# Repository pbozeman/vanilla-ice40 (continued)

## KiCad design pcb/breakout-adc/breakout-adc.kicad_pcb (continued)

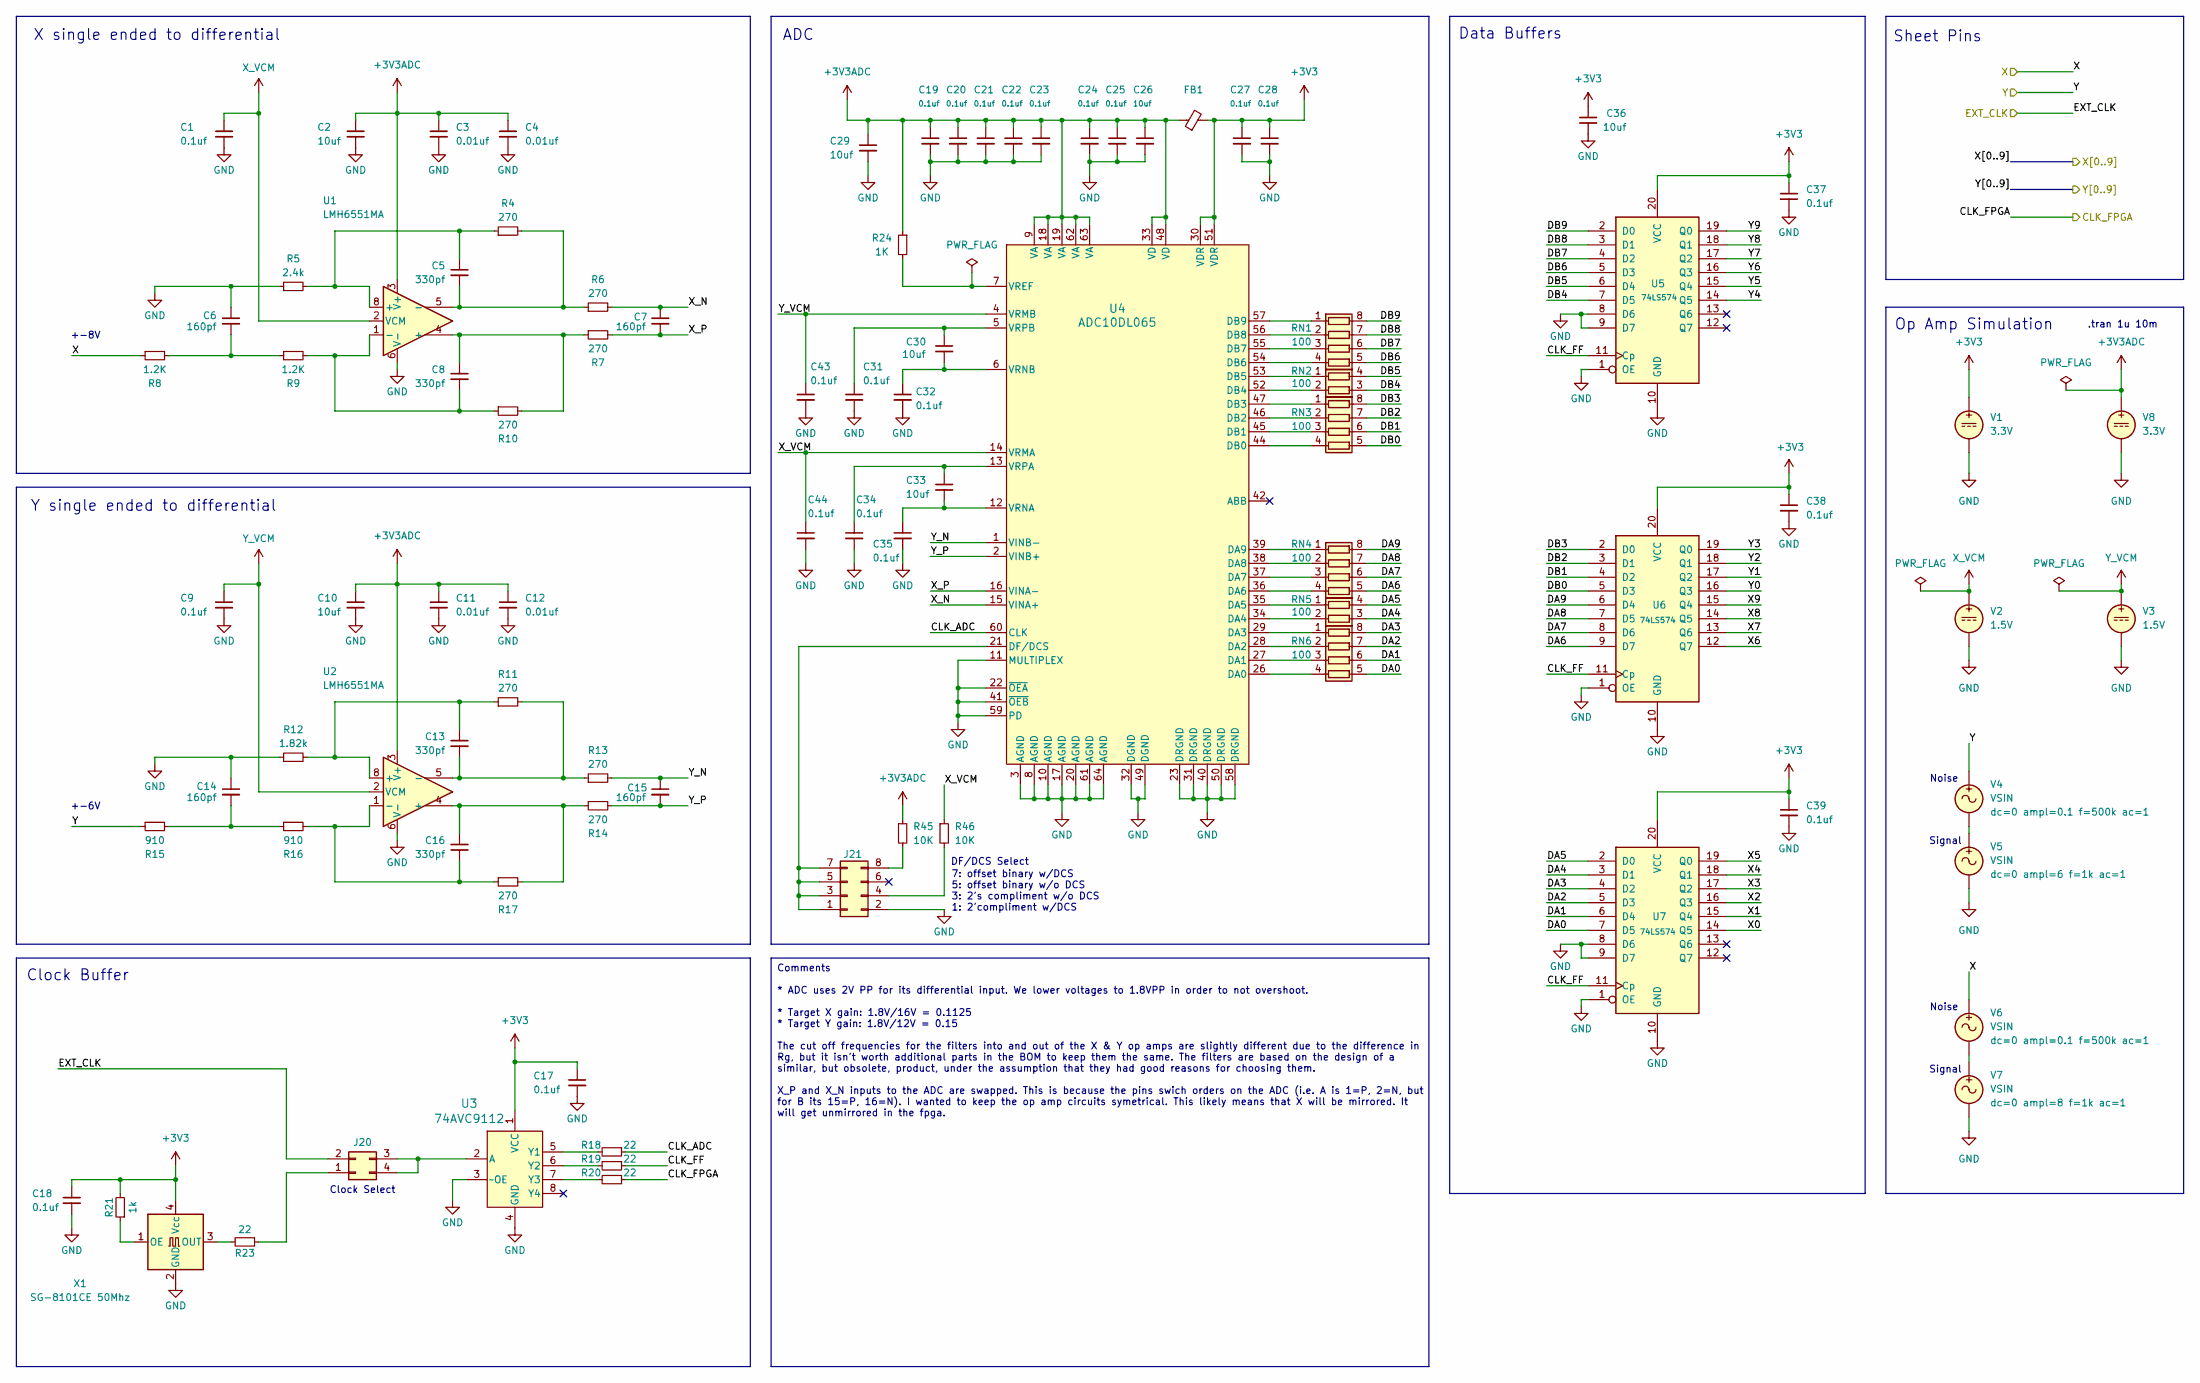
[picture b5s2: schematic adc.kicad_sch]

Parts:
C1, C9, C17, C18, C19, C20, C21, C22, C23, C24, C25, C27, C28, C31, C32, C34, C35, C37, C38, C39, C43, C44: 0.1uf; C_0402_1005Metric; LCSC Part # C71629
C2, C10, C26, C29, C30, C33, C36: 10uf; C_0603_1608Metric; LCSC Part # C77041
C3, C4, C11, C12: 0.01uf; C_0402_1005Metric; LCSC Part # C85735
C5, C8, C13, C16: 330pf; C_0402_1005Metric; Digi-Key Part Number 490-3247-1-ND
C6, C7, C14, C15: 160pf; C_0402_1005Metric; Digi-Key Part Number 490-GRT1555C1H161FA02DCT-ND
FB1: L_0603_1608Metric; LCSC Part # C1002
J20: Conn_02x02_Counter_Clockwise; PinHeader_2x02_P2.54mm_Vertical; Digi-Key Part Number 952-2119-ND
J21: Conn_02x04_Odd_Even; PinHeader_2x04_P2.54mm_Vertical; Digi-Key Part Number 952-2122-ND
R4, R6, R7, R10, R11, R13, R14, R17: 270; R_0603_1608Metric; Digi-Key Part Number YAG1606CT-ND
R5: 2.4k; R_0603_1608Metric; Digi-Key Part Number YAG1619CT-ND
R8, R9: 1.2K; R_0603_1608Metric; Digi-Key Part Number YAG1563CT-ND
R12: 1.82k; R_0603_1608Metric; Digi-Key Part Number YAG1575CT-ND
R15, R16: 910; R_0603_1608Metric; Digi-Key Part Number YAG1748CT-ND
R18, R19, R20, R23: 22; R_0603_1608Metric; LCSC Part # C107701
R21: 1k; R_0603_1608Metric; LCSC Part # C22548
R24: 1K; R_0603_1608Metric; Digi-Key Part Number 311-1.00KHRCT-ND
R45, R46: 10K; R_0603_1608Metric; Digi-Key Part Number 311-10.0KHRCT-ND
RN1, RN3, RN4, RN6: 100; R_Array_Concave_4x0402; LCSC Part # C326873
RN2, RN5: 100; R_Array_Convex_2x0402; Digi-Key Part Number 13-YC122-FR-07100RLCT-ND
U1, U2: LMH6551MA; SOIC-8_3.9x4.9mm_P1.27mm; Digi-Key Part Number LMH6551MA/NOPB-ND
U3: 74AVC9112; VSSOP8_SOT765-1_NEX; Digi-Key Part Number 1727-7845-1-ND
U4: ADC10DL065; VEC64A_TEX; Digi-Key Part Number ADC10DL065CIVS/NOPB-ND
U5, U6, U7: 74LS574; TSSOP-20_4.4x6.5mm_P0.65mm; Digi-Key Part Number 296-8532-1-ND
V1, V8: 3.3V
V2, V3: 1.5V
V4, V5, V6, V7: VSIN
X1: SG-8101CE 50Mhz; Oscillator_SMD_SeikoEpson_SG8002CE-4Pin_3.2x2.5mm; LCSC Part # C390556

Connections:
+3V3: C17.1, C18.1, C27.1, C28.1, C36.1, C37.1, C38.1, C39.1, FB1.2, R21.2, U3.1 (VCC), U4.30 (VDR), U4.51 (VDR), U5.20 (VCC), U6.20 (VCC), U7.20 (VCC), V1.1, X1.4 (Vcc); also elsewhere on the board
+3V3ADC: C2.1, C3.1, C4.1, C10.1, C11.1, C12.1, C19.1, C20.1, C21.1, C22.1, C23.1, C24.1, C25.1, C26.1, C29.1, FB1.1, R24.1, R45.1, U1.3 (V+), U2.3 (V+), U4.9 (VA), U4.18 (VA), U4.19 (VA), U4.33 (VD), U4.48 (VD), U4.62 (VA), U4.63 (VA), V8.1; also elsewhere on the board
/X: R8.1, V6.1; also elsewhere on the board
/Y: R15.1, V4.1; also elsewhere on the board
/adc/CLK_ADC: R18.1, U4.60 (CLK)
/adc/CLK_FF: R19.1, U5.11 (Cp), U6.11 (Cp), U7.11 (Cp)
/adc/DA0: RN6.5 (R4.2), U7.7 (D5)
/adc/DA1: RN6.6 (R3.2), U7.6 (D4)
/adc/DA2: RN6.7 (R2.2), U7.5 (D3)
/adc/DA3: RN6.8 (R1.2), U7.4 (D2)
/adc/DA4: RN5.3 (R2.2), U7.3 (D1)
/adc/DA5: RN5.4 (R1.2), U7.2 (D0)
/adc/DA6: RN4.5 (R4.2), U6.9 (D7)
/adc/DA7: RN4.6 (R3.2), U6.8 (D6)
/adc/DA8: RN4.7 (R2.2), U6.7 (D5)
/adc/DA9: RN4.8 (R1.2), U6.6 (D4)
/adc/DB0: RN3.5 (R4.2), U6.5 (D3)
/adc/DB1: RN3.6 (R3.2), U6.4 (D2)
/adc/DB2: RN3.7 (R2.2), U6.3 (D1)
/adc/DB3: RN3.8 (R1.2), U6.2 (D0)
/adc/DB4: RN2.3 (R2.2), U5.7 (D5)
/adc/DB5: RN2.4 (R1.2), U5.6 (D4)
/adc/DB6: RN1.5 (R4.2), U5.5 (D3)
/adc/DB7: RN1.6 (R3.2), U5.4 (D2)
/adc/DB8: RN1.7 (R2.2), U5.3 (D1)
/adc/DB9: RN1.8 (R1.2), U5.2 (D0)
/adc/X_N: C7.1, R6.2, U4.15 (VINA+)
/adc/X_P: C7.2, R7.2, U4.16 (VINA-)
/adc/Y_N: C15.1, R13.2, U4.1 (VINB-)
/adc/Y_P: C15.2, R14.2, U4.2 (VINB+)
D_12: J20.2; also elsewhere on the board
D_16: R20.1; also elsewhere on the board
D_23: U5.19 (Q0); also elsewhere on the board
D_27: U5.18 (Q1); also elsewhere on the board
D_31: U5.17 (Q2); also elsewhere on the board
D_35: U5.16 (Q3); also elsewhere on the board
D_39: U5.15 (Q4); also elsewhere on the board
D_43: U5.14 (Q5); also elsewhere on the board
D_47: U6.19 (Q0); also elsewhere on the board
D_51: U6.18 (Q1); also elsewhere on the board
D_55: U6.17 (Q2); also elsewhere on the board
D_59: U6.16 (Q3); also elsewhere on the board
D_63: U6.15 (Q4); also elsewhere on the board
D_67: U6.14 (Q5); also elsewhere on the board
D_71: U6.13 (Q6); also elsewhere on the board
D_75: U6.12 (Q7); also elsewhere on the board
D_79: U7.19 (Q0); also elsewhere on the board
D_83: U7.18 (Q1); also elsewhere on the board
D_87: U7.17 (Q2); also elsewhere on the board
D_91: U7.16 (Q3); also elsewhere on the board
D_95: U7.15 (Q4); also elsewhere on the board
D_99: U7.14 (Q5); also elsewhere on the board
GND: C1.2, C2.2, C3.2, C4.2, C6.1, C9.2, C10.2, C11.2, C12.2, C14.1, C17.2, C18.2, C19.2, C20.2, C21.2, C22.2, C23.2, C24.2, C25.2, C26.2, C27.2, C28.2, C29.2, C31.2, C32.2, C34.2, C35.2, C36.2, C37.2, C38.2, C39.2, C43.2, C44.2, J21.2, R5.1, R12.1, U1.6 (V-), U2.6 (V-), U3.3 (~OE), U3.4 (GND), U4.3 (AGND), U4.8 (AGND), U4.10 (AGND), U4.11 (MULTIPLEX), U4.17 (AGND), U4.20 (AGND), U4.22 (~OEA), U4.23 (DRGND), U4.31 (DRGND), U4.32 (DGND), U4.40 (DRGND), U4.41 (~OEB), U4.49 (DGND), U4.50 (DRGND), U4.58 (DRGND), U4.59 (PD), U4.61 (AGND), U4.64 (AGND), U5.1 (OE), U5.8 (D6), U5.9 (D7), U5.10 (GND), U6.1 (OE), U6.10 (GND), U7.1 (OE), U7.8 (D6), U7.9 (D7), U7.10 (GND), V1.2, V2.2, V3.2, V5.2, V7.2, V8.2, X1.2 (GND); also elsewhere on the board
unnamed: C5.1, R4.1, R5.2, U1.8 (+)
unnamed: C5.2, R4.2, R6.1, U1.5 (-)
unnamed: C6.2, R8.2, R9.1
unnamed: C8.1, R7.1, R10.2, U1.4 (+)
unnamed: C8.2, R9.2, R10.1, U1.1 (-)
unnamed: C13.1, R11.1, R12.2, U2.8 (+)
unnamed: C13.2, R11.2, R13.1, U2.5 (-)
unnamed: C14.2, R15.2, R16.1
unnamed: C16.1, R14.1, R17.2, U2.4 (+)
unnamed: C16.2, R16.2, R17.1, U2.1 (-)
unnamed: J20.1, R23.1
unnamed: J20.3, J20.4, U3.2 (A)
unnamed: J21.1, J21.3, J21.5, J21.7, U4.21 (DF/DCS)
unnamed: J21.4, R46.2
unnamed: J21.8, R45.2
unnamed: RN1.1 (R1.1), U4.57 (DB9)
unnamed: RN1.2 (R2.1), U4.56 (DB8)
unnamed: RN1.3 (R3.1), U4.55 (DB7)
unnamed: RN1.4 (R4.1), U4.54 (DB6)
unnamed: RN2.1 (R1.1), U4.53 (DB5)
unnamed: RN2.2 (R2.1), U4.52 (DB4)
unnamed: RN3.1 (R1.1), U4.47 (DB3)
unnamed: RN3.2 (R2.1), U4.46 (DB2)
unnamed: RN3.3 (R3.1), U4.45 (DB1)
unnamed: RN3.4 (R4.1), U4.44 (DB0)
unnamed: RN4.1 (R1.1), U4.39 (DA9)
unnamed: RN4.2 (R2.1), U4.38 (DA8)
unnamed: RN4.3 (R3.1), U4.37 (DA7)
unnamed: RN4.4 (R4.1), U4.36 (DA6)
unnamed: RN5.1 (R1.1), U4.35 (DA5)
unnamed: RN5.2 (R2.1), U4.34 (DA4)
unnamed: RN6.1 (R1.1), U4.29 (DA3)
unnamed: RN6.2 (R2.1), U4.28 (DA2)
unnamed: RN6.3 (R3.1), U4.27 (DA1)
unnamed: RN6.4 (R4.1), U4.26 (DA0)
unnamed: R18.2, U3.5 (Y1)
unnamed: R19.2, U3.6 (Y2)
unnamed: R20.2, U3.7 (Y3)
unnamed: R24.2, U4.7 (VREF)
unnamed: C33.2, C35.1, U4.12 (VRNA)
unnamed: C30.2, C32.1, U4.6 (VRNB)
unnamed: C33.1, C34.1, U4.13 (VRPA)
unnamed: C30.1, C31.1, U4.5 (VRPB)
unnamed: V4.2, V5.1
unnamed: V6.2, V7.1
unnamed: R21.1, X1.1 (OE)
unnamed: R23.2, X1.3 (OUT)
X_VCM: C1.1, C44.1, R46.1, U1.2 (VCM), U4.14 (VRMA), V2.1; also elsewhere on the board
Y_VCM: C9.1, C43.1, U2.2 (VCM), U4.4 (VRMB), V3.1; also elsewhere on the board

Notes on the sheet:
Comments * ADC uses 2V PP for its differential input. We lower voltages to 1.8VPP in order to not overshoot. * Target X gain: 1.8V/16V = 0.1125 * Target Y gain: 1.8V/12V = 0.15 The cut off frequencies for the filters into and out of the X & Y op amps are slightly different due to the difference in 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
Y single ended to differential
7: offset binary w/DCS 5: offset binary w/o DCS 3: 2's compliment w/o DCS 1: 2'compliment w/DCS
+-8V
Signal
Data Buffers
Clock Select
.tran 1u 10m
X single ended to differential
Noise
ADC
Sheet Pins
Op Amp Simulation
+-6V
DF/DCS Select
Clock Buffer

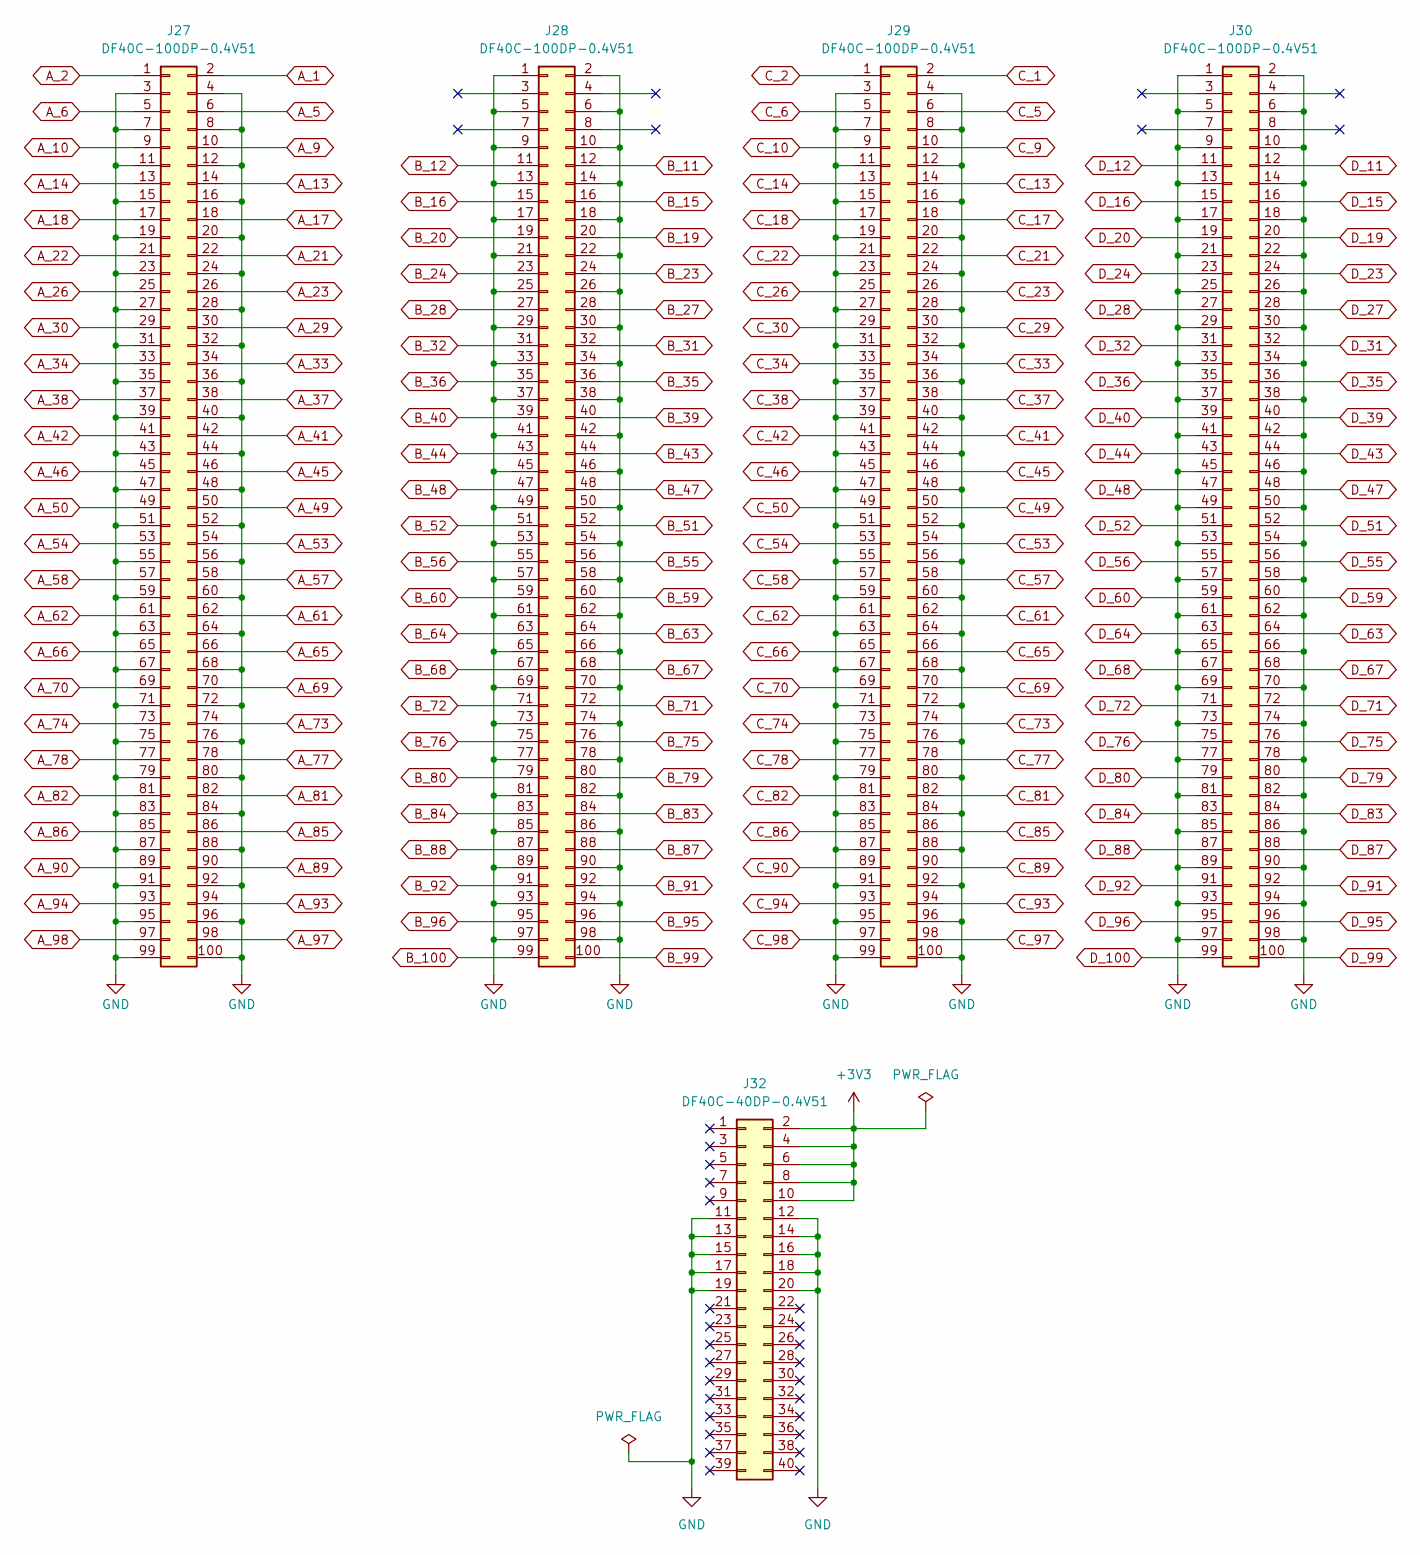
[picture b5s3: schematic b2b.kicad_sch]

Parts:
J27, J28, J29, J30: DF40C-100DP-0.4V51; DF40C100DP04V51; Digi-Key Part Number H11615CT-ND
J32: DF40C-40DP-0.4V51; DF40C40DP04V51; Digi-Key Part Number H11625CT-ND

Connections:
+3V3: J32.2, J32.4, J32.6, J32.8, J32.10; also elsewhere on the board
A_1: J27.2
A_2: J27.1
A_5: J27.6
A_6: J27.5
A_9: J27.10
A_10: J27.9
A_13: J27.14
A_14: J27.13
A_17: J27.18
A_18: J27.17
A_21: J27.22
A_22: J27.21
A_23: J27.26
A_26: J27.25
A_29: J27.30
A_30: J27.29
A_33: J27.34
A_34: J27.33
A_37: J27.38
A_38: J27.37
A_41: J27.42
A_42: J27.41
A_45: J27.46
A_46: J27.45
A_49: J27.50
A_50: J27.49
A_53: J27.54
A_54: J27.53
A_57: J27.58
A_58: J27.57
A_61: J27.62
A_62: J27.61
A_65: J27.66
A_66: J27.65
A_69: J27.70
A_70: J27.69
A_73: J27.74
A_74: J27.73
A_77: J27.78
A_78: J27.77
A_81: J27.82
A_82: J27.81
A_85: J27.86
A_86: J27.85
A_89: J27.90
A_90: J27.89
A_93: J27.94
A_94: J27.93
A_97: J27.98
A_98: J27.97
B_11: J28.12
B_12: J28.11
B_15: J28.16
B_16: J28.15
B_19: J28.20
B_20: J28.19
B_23: J28.24
B_24: J28.23
B_27: J28.28
B_28: J28.27
B_31: J28.32
B_32: J28.31
B_35: J28.36
B_36: J28.35
B_39: J28.40
B_40: J28.39
B_43: J28.44
B_44: J28.43
B_47: J28.48
B_48: J28.47
B_51: J28.52
B_52: J28.51
B_55: J28.56
B_56: J28.55
B_59: J28.60
B_60: J28.59
B_63: J28.64
B_64: J28.63
B_67: J28.68
B_68: J28.67
B_71: J28.72
B_72: J28.71
B_75: J28.76
B_76: J28.75
B_79: J28.80
B_80: J28.79
B_83: J28.84
B_84: J28.83
B_87: J28.88
B_88: J28.87
B_91: J28.92
B_92: J28.91
B_95: J28.96
B_96: J28.95
B_99: J28.100
B_100: J28.99
C_1: J29.2
C_2: J29.1
C_5: J29.6
C_6: J29.5
C_9: J29.10
C_10: J29.9
C_13: J29.14
C_14: J29.13
C_17: J29.18
C_18: J29.17
C_21: J29.22
C_22: J29.21
C_23: J29.26
C_26: J29.25
C_29: J29.30
C_30: J29.29
C_33: J29.34
C_34: J29.33
C_37: J29.38
C_38: J29.37
C_41: J29.42
C_42: J29.41
C_45: J29.46
C_46: J29.45
C_49: J29.50
C_50: J29.49
C_53: J29.54
C_54: J29.53
C_57: J29.58
C_58: J29.57; also elsewhere on the board
C_61: J29.62
C_62: J29.61; also elsewhere on the board
C_65: J29.66
C_66: J29.65; also elsewhere on the board
C_69: J29.70
C_70: J29.69; also elsewhere on the board
C_73: J29.74
C_74: J29.73; also elsewhere on the board
C_77: J29.78
C_78: J29.77; also elsewhere on the board
C_81: J29.82
C_82: J29.81; also elsewhere on the board
C_85: J29.86
C_86: J29.85; also elsewhere on the board
C_89: J29.90
C_90: J29.89; also elsewhere on the board
C_93: J29.94
C_94: J29.93; also elsewhere on the board
C_97: J29.98
C_98: J29.97; also elsewhere on the board
D_11: J30.12; also elsewhere on the board
D_12: J30.11; also elsewhere on the board
D_15: J30.16; also elsewhere on the board
D_16: J30.15; also elsewhere on the board
D_19: J30.20; also elsewhere on the board
D_20: J30.19; also elsewhere on the board
D_23: J30.24; also elsewhere on the board
D_24: J30.23; also elsewhere on the board
D_27: J30.28; also elsewhere on the board
D_28: J30.27; also elsewhere on the board
D_31: J30.32; also elsewhere on the board
D_32: J30.31
D_35: J30.36; also elsewhere on the board
D_36: J30.35
D_39: J30.40; also elsewhere on the board
D_40: J30.39
D_43: J30.44; also elsewhere on the board
D_44: J30.43
D_47: J30.48; also elsewhere on the board
D_48: J30.47
D_51: J30.52; also elsewhere on the board
D_52: J30.51
D_55: J30.56; also elsewhere on the board
D_56: J30.55
D_59: J30.60; also elsewhere on the board
D_60: J30.59
D_63: J30.64; also elsewhere on the board
D_64: J30.63
D_67: J30.68; also elsewhere on the board
D_68: J30.67
D_71: J30.72; also elsewhere on the board
D_72: J30.71
D_75: J30.76; also elsewhere on the board
D_76: J30.75
D_79: J30.80; also elsewhere on the board
D_80: J30.79
D_83: J30.84; also elsewhere on the board
D_84: J30.83
D_87: J30.88; also elsewhere on the board
D_88: J30.87
D_91: J30.92; also elsewhere on the board
D_92: J30.91
D_95: J30.96; also elsewhere on the board
D_96: J30.95
D_99: J30.100; also elsewhere on the board
D_100: J30.99
GND: J27.3, J27.4, J27.7, J27.8, J27.11, J27.12, J27.15, J27.16, J27.19, J27.20, J27.23, J27.24, J27.27, J27.28, J27.31, J27.32, J27.35, J27.36, J27.39, J27.40, J27.43, J27.44, J27.47, J27.48, J27.51, J27.52, J27.55, J27.56, J27.59, J27.60, J27.63, J27.64, J27.67, J27.68, J27.71, J27.72, J27.75, J27.76, J27.79, J27.80, J27.83, J27.84, J27.87, J27.88, J27.91, J27.92, J27.95, J27.96, J27.99, J27.100, J28.1, J28.2, J28.5, J28.6, J28.9, J28.10, J28.13, J28.14, J28.17, J28.18, J28.21, J28.22, J28.25, J28.26, J28.29, J28.30, J28.33, J28.34, J28.37, J28.38, J28.41, J28.42, J28.45, J28.46, J28.49, J28.50, J28.53, J28.54, J28.57, J28.58, J28.61, J28.62, J28.65, J28.66, J28.69, J28.70, J28.73, J28.74, J28.77, J28.78, J28.81, J28.82, J28.85, J28.86, J28.89, J28.90, J28.93, J28.94, J28.97, J28.98, J29.3, J29.4, J29.7, J29.8, J29.11, J29.12, J29.15, J29.16, J29.19, J29.20, J29.23, J29.24, J29.27, J29.28, J29.31, J29.32, J29.35, J29.36, J29.39, J29.40, J29.43, J29.44, J29.47, J29.48, J29.51, J29.52, J29.55, J29.56, J29.59, J29.60, J29.63, J29.64, J29.67, J29.68, J29.71, J29.72, J29.75, J29.76, J29.79, J29.80, J29.83, J29.84, J29.87, J29.88, J29.91, J29.92, J29.95, J29.96, J29.99, J29.100, J30.1, J30.2, J30.5, J30.6, J30.9, J30.10, J30.13, J30.14, J30.17, J30.18, J30.21, J30.22, J30.25, J30.26, J30.29, J30.30, J30.33, J30.34, J30.37, J30.38, J30.41, J30.42, J30.45, J30.46, J30.49, J30.50, J30.53, J30.54, J30.57, J30.58, J30.61, J30.62, J30.65, J30.66, J30.69, J30.70, J30.73, J30.74, J30.77, J30.78, J30.81, J30.82, J30.85, J30.86, J30.89, J30.90, J30.93, J30.94, J30.97, J30.98, J32.11, J32.12, J32.13, J32.14, J32.15, J32.16, J32.17, J32.18, J32.19, J32.20; also elsewhere on the board

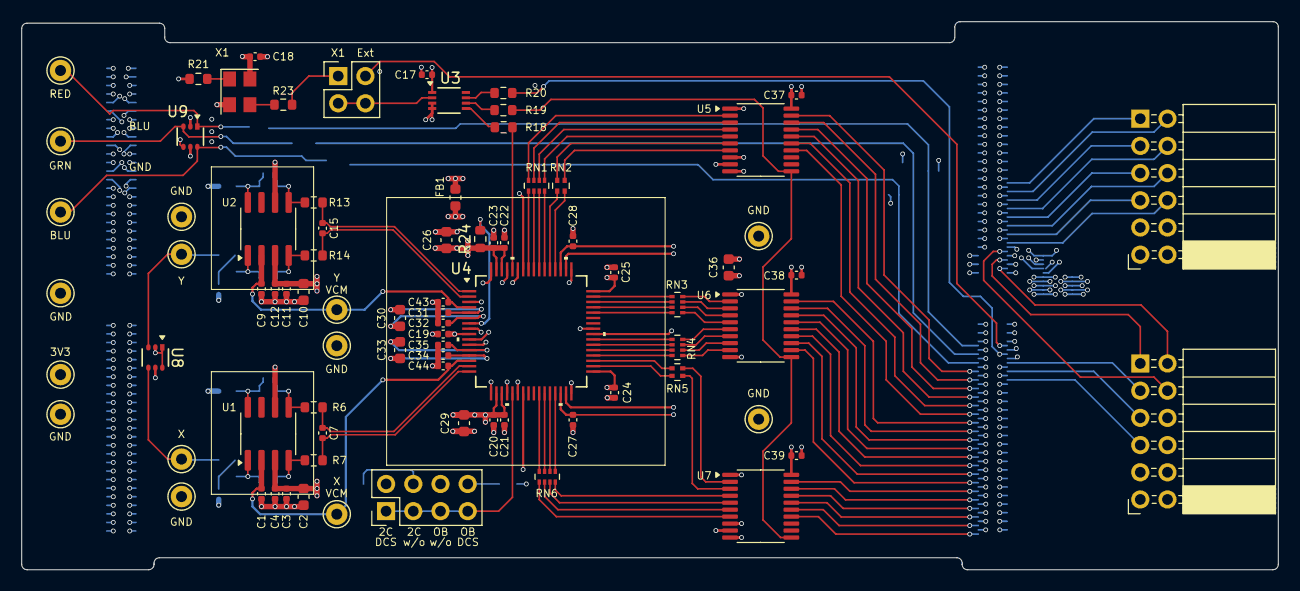
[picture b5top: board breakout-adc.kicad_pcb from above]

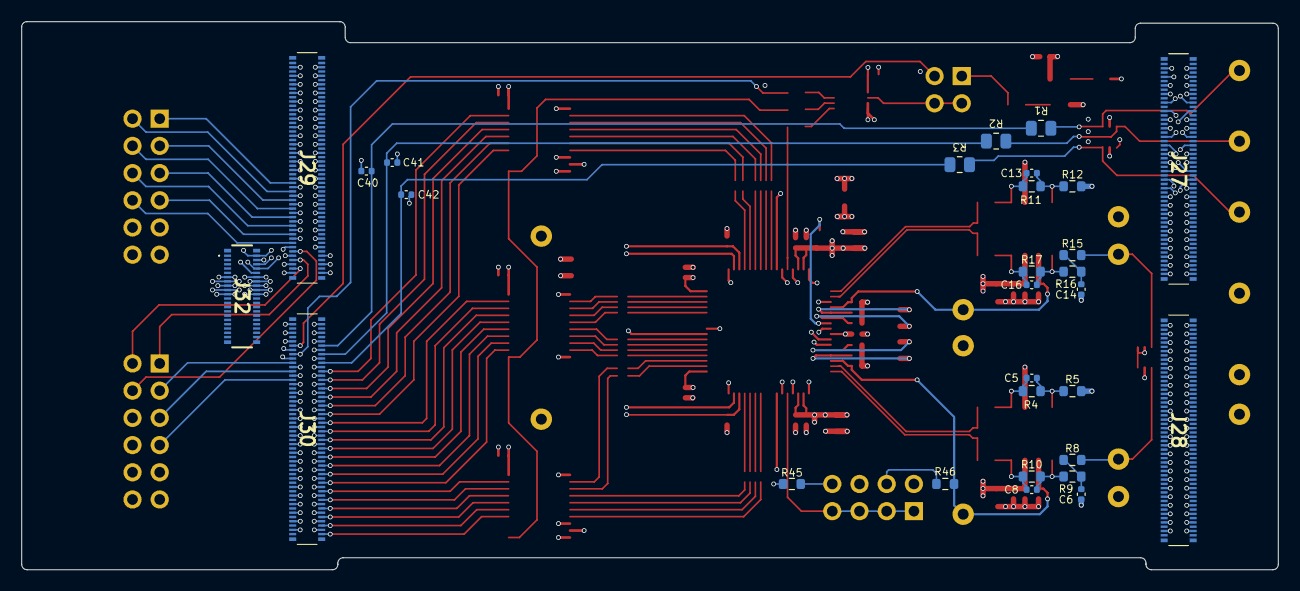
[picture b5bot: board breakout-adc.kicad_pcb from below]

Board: 4 copper layers, 117.4 x 51.2 mm, 110 parts (29 on the bottom side), 120 nets.

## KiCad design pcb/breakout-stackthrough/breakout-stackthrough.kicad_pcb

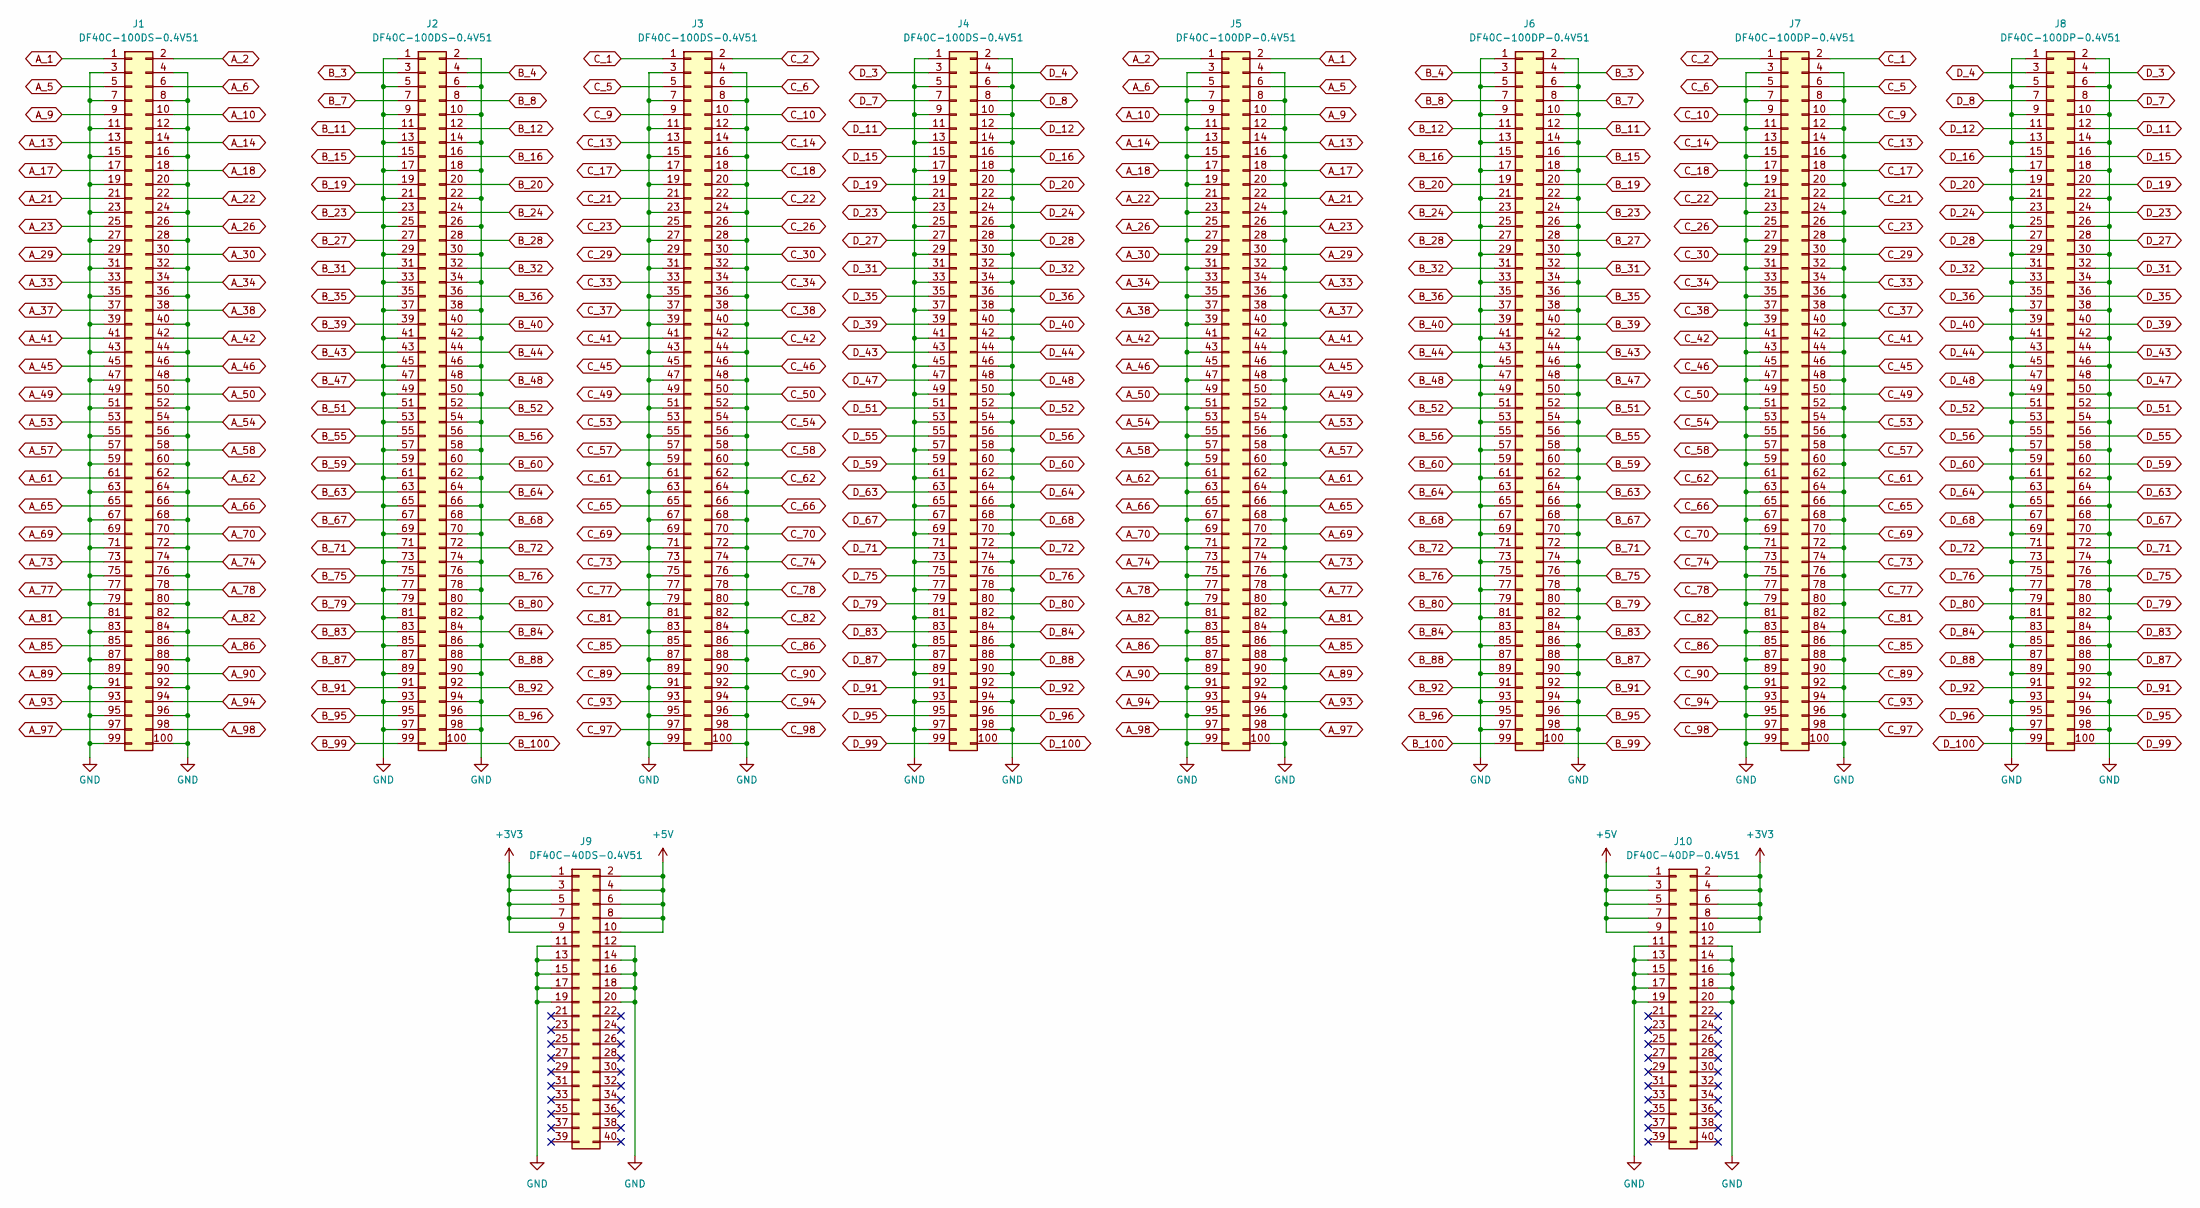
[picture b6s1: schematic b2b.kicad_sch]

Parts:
J1, J2, J3, J4: DF40C-100DS-0.4V51; DF40C100DS04V51; Digi-Key Part Number H11615CT-ND
J5, J6, J7, J8: DF40C-100DP-0.4V51; DF40C100DP04V51; Digi-Key Part Number H11615CT-ND
J9: DF40C-40DS-0.4V51; DF40C40DS04V51; Digi-Key Part Number H11625CT-ND
J10: DF40C-40DP-0.4V51; DF40C40DP04V51; Digi-Key Part Number H11625CT-ND

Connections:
+3V3: J9.1, J9.3, J9.5, J9.7, J9.9, J10.2, J10.4, J10.6, J10.8, J10.10
+5V: J9.2, J9.4, J9.6, J9.8, J9.10, J10.1, J10.3, J10.5, J10.7, J10.9
A_1: J1.1, J5.2
A_2: J1.2, J5.1
A_5: J1.5, J5.6
A_6: J1.6, J5.5
A_9: J1.9, J5.10
A_10: J1.10, J5.9
A_13: J1.13, J5.14
A_14: J1.14, J5.13
A_17: J1.17, J5.18
A_18: J1.18, J5.17
A_21: J1.21, J5.22
A_22: J1.22, J5.21
A_23: J1.25, J5.26
A_26: J1.26, J5.25
A_29: J1.29, J5.30
A_30: J1.30, J5.29
A_33: J1.33, J5.34
A_34: J1.34, J5.33
A_37: J1.37, J5.38
A_38: J1.38, J5.37
A_41: J1.41, J5.42
A_42: J1.42, J5.41
A_45: J1.45, J5.46
A_46: J1.46, J5.45
A_49: J1.49, J5.50
A_50: J1.50, J5.49
A_53: J1.53, J5.54
A_54: J1.54, J5.53
A_57: J1.57, J5.58
A_58: J1.58, J5.57
A_61: J1.61, J5.62
A_62: J1.62, J5.61
A_65: J1.65, J5.66
A_66: J1.66, J5.65
A_69: J1.69, J5.70
A_70: J1.70, J5.69
A_73: J1.73, J5.74
A_74: J1.74, J5.73
A_77: J1.77, J5.78
A_78: J1.78, J5.77
A_81: J1.81, J5.82
A_82: J1.82, J5.81
A_85: J1.85, J5.86
A_86: J1.86, J5.85
A_89: J1.89, J5.90
A_90: J1.90, J5.89
A_93: J1.93, J5.94
A_94: J1.94, J5.93
A_97: J1.97, J5.98
A_98: J1.98, J5.97
B_3: J2.3, J6.4
B_4: J2.4, J6.3
B_7: J2.7, J6.8
B_8: J2.8, J6.7
B_11: J2.11, J6.12
B_12: J2.12, J6.11
B_15: J2.15, J6.16
B_16: J2.16, J6.15
B_19: J2.19, J6.20
B_20: J2.20, J6.19
B_23: J2.23, J6.24
B_24: J2.24, J6.23
B_27: J2.27, J6.28
B_28: J2.28, J6.27
B_31: J2.31, J6.32
B_32: J2.32, J6.31
B_35: J2.35, J6.36
B_36: J2.36, J6.35
B_39: J2.39, J6.40
B_40: J2.40, J6.39
B_43: J2.43, J6.44
B_44: J2.44, J6.43
B_47: J2.47, J6.48
B_48: J2.48, J6.47
B_51: J2.51, J6.52
B_52: J2.52, J6.51
B_55: J2.55, J6.56
B_56: J2.56, J6.55
B_59: J2.59, J6.60
B_60: J2.60, J6.59
B_63: J2.63, J6.64
B_64: J2.64, J6.63
B_67: J2.67, J6.68
B_68: J2.68, J6.67
B_71: J2.71, J6.72
B_72: J2.72, J6.71
B_75: J2.75, J6.76
B_76: J2.76, J6.75
B_79: J2.79, J6.80
B_80: J2.80, J6.79
B_83: J2.83, J6.84
B_84: J2.84, J6.83
B_87: J2.87, J6.88
B_88: J2.88, J6.87
B_91: J2.91, J6.92
B_92: J2.92, J6.91
B_95: J2.95, J6.96
B_96: J2.96, J6.95
B_99: J2.99, J6.100
B_100: J2.100, J6.99
C_1: J3.1, J7.2
C_2: J3.2, J7.1
C_5: J3.5, J7.6
C_6: J3.6, J7.5
C_9: J3.9, J7.10
C_10: J3.10, J7.9
C_13: J3.13, J7.14
C_14: J3.14, J7.13
C_17: J3.17, J7.18
C_18: J3.18, J7.17
C_21: J3.21, J7.22
C_22: J3.22, J7.21
C_23: J3.25, J7.26
C_26: J3.26, J7.25
C_29: J3.29, J7.30
C_30: J3.30, J7.29
C_33: J3.33, J7.34
C_34: J3.34, J7.33
C_37: J3.37, J7.38
C_38: J3.38, J7.37
C_41: J3.41, J7.42
C_42: J3.42, J7.41
C_45: J3.45, J7.46
C_46: J3.46, J7.45
C_49: J3.49, J7.50
C_50: J3.50, J7.49
C_53: J3.53, J7.54
C_54: J3.54, J7.53
C_57: J3.57, J7.58
C_58: J3.58, J7.57
C_61: J3.61, J7.62
C_62: J3.62, J7.61
C_65: J3.65, J7.66
C_66: J3.66, J7.65
C_69: J3.69, J7.70
C_70: J3.70, J7.69
C_73: J3.73, J7.74
C_74: J3.74, J7.73
C_77: J3.77, J7.78
C_78: J3.78, J7.77
C_81: J3.81, J7.82
C_82: J3.82, J7.81
C_85: J3.85, J7.86
C_86: J3.86, J7.85
C_89: J3.89, J7.90
C_90: J3.90, J7.89
C_93: J3.93, J7.94
C_94: J3.94, J7.93
C_97: J3.97, J7.98
C_98: J3.98, J7.97
D_3: J4.3, J8.4
D_4: J4.4, J8.3
D_7: J4.7, J8.8
D_8: J4.8, J8.7
D_11: J4.11, J8.12
D_12: J4.12, J8.11
D_15: J4.15, J8.16
D_16: J4.16, J8.15
D_19: J4.19, J8.20
D_20: J4.20, J8.19
D_23: J4.23, J8.24
D_24: J4.24, J8.23
D_27: J4.27, J8.28
D_28: J4.28, J8.27
D_31: J4.31, J8.32
D_32: J4.32, J8.31
D_35: J4.35, J8.36
D_36: J4.36, J8.35
D_39: J4.39, J8.40
D_40: J4.40, J8.39
D_43: J4.43, J8.44
D_44: J4.44, J8.43
D_47: J4.47, J8.48
D_48: J4.48, J8.47
D_51: J4.51, J8.52
D_52: J4.52, J8.51
D_55: J4.55, J8.56
D_56: J4.56, J8.55
D_59: J4.59, J8.60
D_60: J4.60, J8.59
D_63: J4.63, J8.64
D_64: J4.64, J8.63
D_67: J4.67, J8.68
D_68: J4.68, J8.67
D_71: J4.71, J8.72
D_72: J4.72, J8.71
D_75: J4.75, J8.76
D_76: J4.76, J8.75
D_79: J4.79, J8.80
D_80: J4.80, J8.79
D_83: J4.83, J8.84
D_84: J4.84, J8.83
D_87: J4.87, J8.88
D_88: J4.88, J8.87
D_91: J4.91, J8.92
D_92: J4.92, J8.91
D_95: J4.95, J8.96
D_96: J4.96, J8.95
D_99: J4.99, J8.100
D_100: J4.100, J8.99
GND: J1.3, J1.4, J1.7, J1.8, J1.11, J1.12, J1.15, J1.16, J1.19, J1.20, J1.23, J1.24, J1.27, J1.28, J1.31, J1.32, J1.35, J1.36, J1.39, J1.40, J1.43, J1.44, J1.47, J1.48, J1.51, J1.52, J1.55, J1.56, J1.59, J1.60, J1.63, J1.64, J1.67, J1.68, J1.71, J1.72, J1.75, J1.76, J1.79, J1.80, J1.83, J1.84, J1.87, J1.88, J1.91, J1.92, J1.95, J1.96, J1.99, J1.100, J2.1, J2.2, J2.5, J2.6, J2.9, J2.10, J2.13, J2.14, J2.17, J2.18, J2.21, J2.22, J2.25, J2.26, J2.29, J2.30, J2.33, J2.34, J2.37, J2.38, J2.41, J2.42, J2.45, J2.46, J2.49, J2.50, J2.53, J2.54, J2.57, J2.58, J2.61, J2.62, J2.65, J2.66, J2.69, J2.70, J2.73, J2.74, J2.77, J2.78, J2.81, J2.82, J2.85, J2.86, J2.89, J2.90, J2.93, J2.94, J2.97, J2.98, J3.3, J3.4, J3.7, J3.8, J3.11, J3.12, J3.15, J3.16, J3.19, J3.20, J3.23, J3.24, J3.27, J3.28, J3.31, J3.32, J3.35, J3.36, J3.39, J3.40, J3.43, J3.44, J3.47, J3.48, J3.51, J3.52, J3.55, J3.56, J3.59, J3.60, J3.63, J3.64, J3.67, J3.68, J3.71, J3.72, J3.75, J3.76, J3.79, J3.80, J3.83, J3.84, J3.87, J3.88, J3.91, J3.92, J3.95, J3.96, J3.99, J3.100, J4.1, J4.2, J4.5, J4.6, J4.9, J4.10, J4.13, J4.14, J4.17, J4.18, J4.21, J4.22, J4.25, J4.26, J4.29, J4.30, J4.33, J4.34, J4.37, J4.38, J4.41, J4.42, J4.45, J4.46, J4.49, J4.50, J4.53, J4.54, J4.57, J4.58, J4.61, J4.62, J4.65, J4.66, J4.69, J4.70, J4.73, J4.74, J4.77, J4.78, J4.81, J4.82, J4.85, J4.86, J4.89, J4.90, J4.93, J4.94, J4.97, J4.98, J5.3, J5.4, J5.7, J5.8, J5.11, J5.12, J5.15, J5.16, J5.19, J5.20, J5.23, J5.24, J5.27, J5.28, J5.31, J5.32, J5.35, J5.36, J5.39, J5.40, J5.43, J5.44, J5.47, J5.48, J5.51, J5.52, J5.55, J5.56, J5.59, J5.60, J5.63, J5.64, J5.67, J5.68, J5.71, J5.72, J5.75, J5.76, J5.79, J5.80, J5.83, J5.84, J5.87, J5.88, J5.91, J5.92, J5.95, J5.96, J5.99, J5.100, J6.1, J6.2, J6.5, J6.6, J6.9, J6.10, J6.13, J6.14, J6.17, J6.18, J6.21, J6.22, J6.25, J6.26, J6.29, J6.30, J6.33, J6.34, J6.37, J6.38, J6.41, J6.42, J6.45, J6.46, J6.49, J6.50, J6.53, J6.54, J6.57, J6.58, J6.61, J6.62, J6.65, J6.66, J6.69, J6.70, J6.73, J6.74, J6.77, J6.78, J6.81, J6.82, J6.85, J6.86, J6.89, J6.90, J6.93, J6.94, J6.97, J6.98, J7.3, J7.4, J7.7, J7.8, J7.11, J7.12, J7.15, J7.16, J7.19, J7.20, J7.23, J7.24, J7.27, J7.28, J7.31, J7.32, J7.35, J7.36, J7.39, J7.40, J7.43, J7.44, J7.47, J7.48, J7.51, J7.52, J7.55, J7.56, J7.59, J7.60, J7.63, J7.64, J7.67, J7.68, J7.71, J7.72, J7.75, J7.76, J7.79, J7.80, J7.83, J7.84, J7.87, J7.88, J7.91, J7.92, J7.95, J7.96, J7.99, J7.100, J8.1, J8.2, J8.5, J8.6, J8.9, J8.10, J8.13, J8.14, J8.17, J8.18, J8.21, J8.22, J8.25, J8.26, J8.29, J8.30, J8.33, J8.34, J8.37, J8.38, J8.41, J8.42, J8.45, J8.46, J8.49, J8.50, J8.53, J8.54, J8.57, J8.58, J8.61, J8.62, J8.65, J8.66, J8.69, J8.70, J8.73, J8.74, J8.77, J8.78, J8.81, J8.82, J8.85, J8.86, J8.89, J8.90, J8.93, J8.94, J8.97, J8.98, J9.11, J9.12, J9.13, J9.14, J9.15, J9.16, J9.17, J9.18, J9.19, J9.20, J10.11, J10.12, J10.13, J10.14, J10.15, J10.16, J10.17, J10.18, J10.19, J10.20

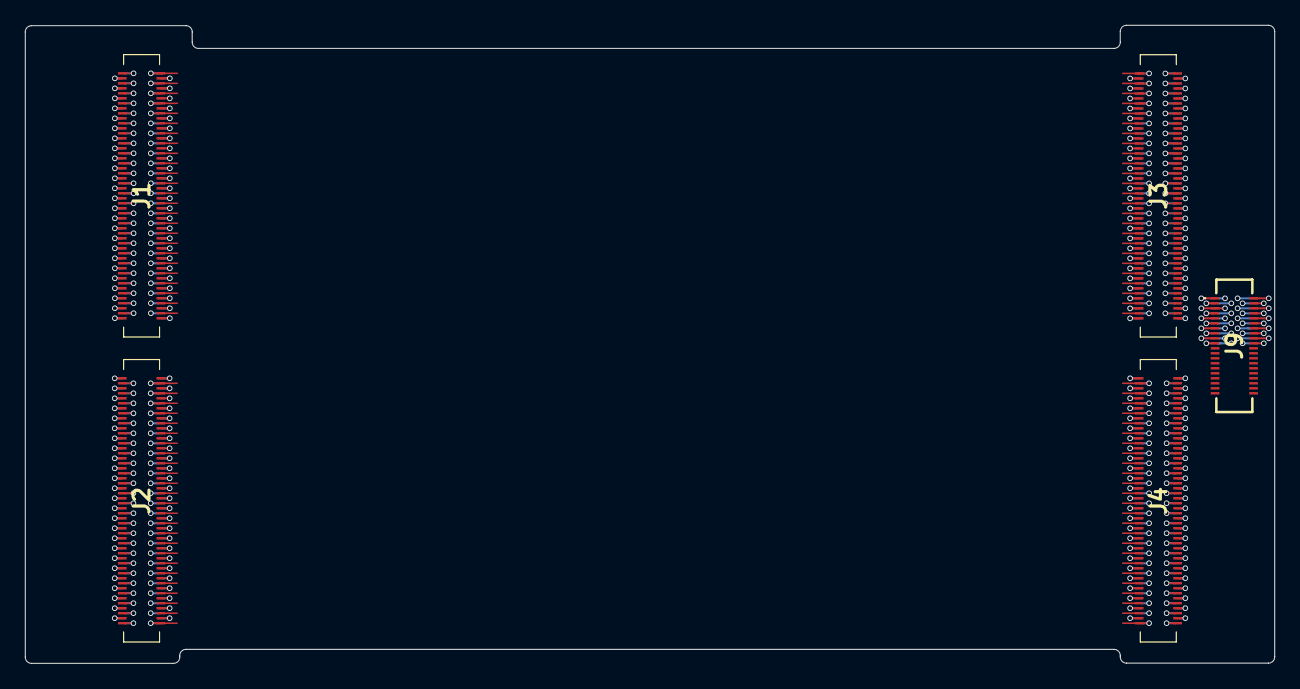
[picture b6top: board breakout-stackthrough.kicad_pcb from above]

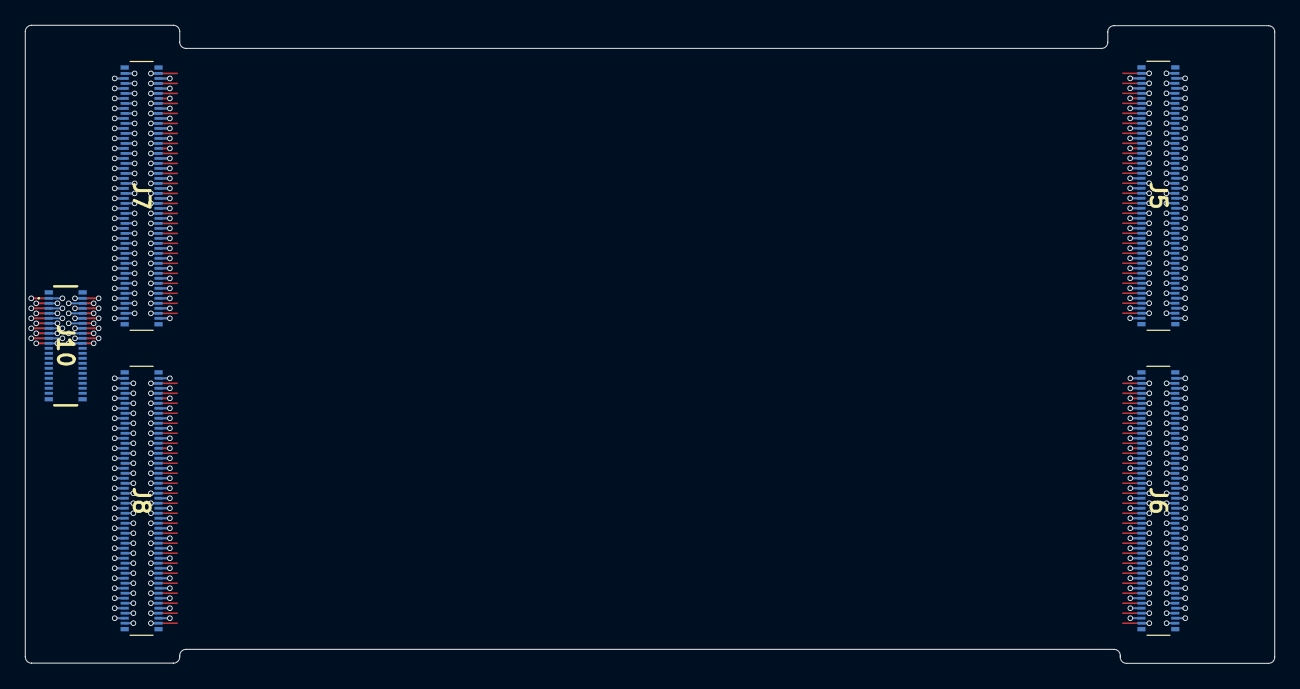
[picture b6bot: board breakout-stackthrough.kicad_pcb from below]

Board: 6 copper layers, 100.0 x 51.1 mm, 10 parts (5 on the bottom side), 203 nets.
